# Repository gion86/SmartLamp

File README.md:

# SMART LAMP
### Smart lamp to wakeup with sunrise
##### SMD version

The project is a LED strip control board to generate a smart wakeup light, which 
simulates the sunrise light.
On board there is a real time clock, to  keep track of the actual date and time 
even on power loss, and some MOSFET to drive the LEDs with PWM.
On a separate breakout board I'm using a BLE chipset to connect with an Android 
application, to setup date, time, alarms and LED light.

Everything is soldered on the same PCB. The micro is an Atmel ATMega328P.

The project is compiled for Atmel AVR, with standard AVR GCC toolchain. 
Eclipse was used to create and compile the projects, with the AVR Eclipse Plugin.

This project consists of a main C++ file and some libraries:

* **DS3232RTC** : real time clock library, to read the actual date and time. The library 
  have been modified to work with the an external instance of the I2C bus control 
  class, and each functionality has been tested with the hardware (reference <https://github.com/gion86/DS3232RTC>);
* **TimeZone** : Arduino library to account for DST (summer time) with the RTC clock
  (reference <https://github.com/gion86/Timezone>, version with time.h from avr-libc);
* **Wire** : I2C library for Atmel micros. The library includes the correct source file for 
  the hardware used (reference <https://github.com/gion86/Wire>); 
  In the case of the Mega micro the I2C hardware module is used with the TwoWire 
  library (reference <https://github.com/esp8266/Arduino/tree/master/libraries/Wire>);
* **ATMega core**  (reference <https://github.com/gion86/ArduinoCore> and 
  <https://github.com/arduino/Arduino/tree/master/hardware/arduino/avr/cores/arduino>)

The project folder contains:

* Android application for Bluetooth Low Energy communication;
* the bill of material;
* datasheet of used components;
* electrical schematic and board (made with Eagle);

Some pictures can be found at https://photos.app.goo.gl/nYQq9dkLF3Ui9xUt2

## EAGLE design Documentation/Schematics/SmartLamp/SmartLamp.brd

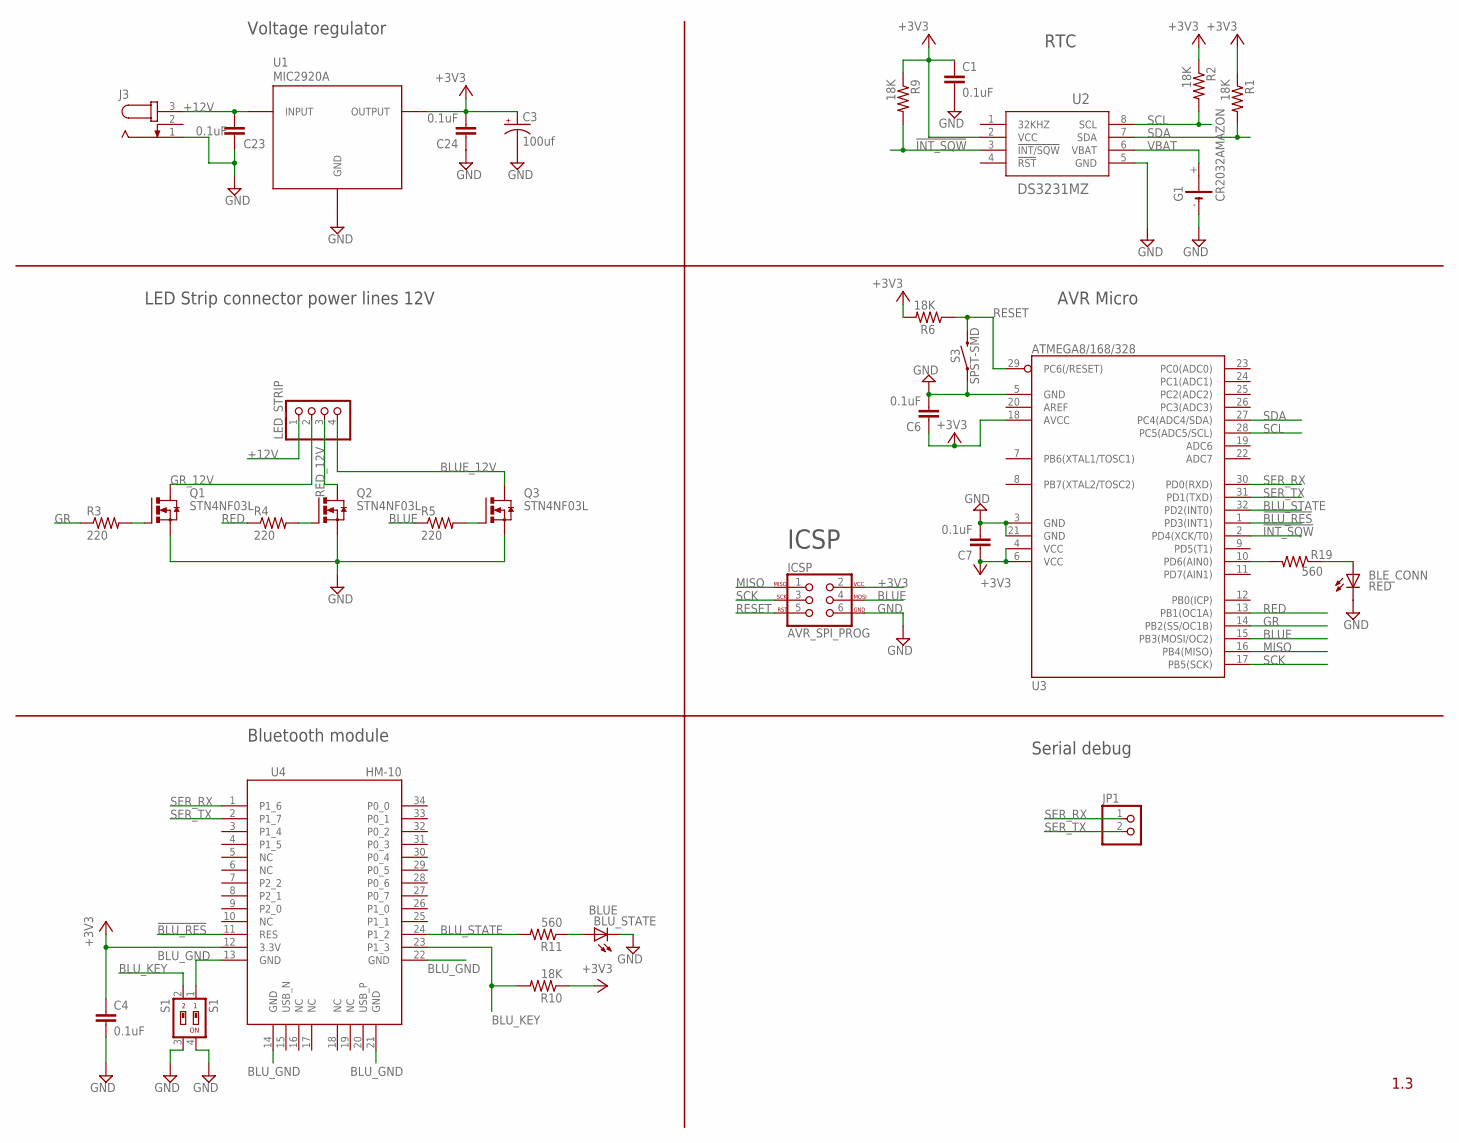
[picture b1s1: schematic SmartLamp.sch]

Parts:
BLE_CONN: RED; CHIPLED_1206
BLU_STATE: BLUE; CHIPLED_1206
C1, C4, C6, C7, C23, C24: 0.1uF; C1206
C3: 100uf; PANASONIC_C
G1: CR2032AMAZON; CR2032_AMAZON
ICSP: AVR_SPI_PROG; 2X3
J3: JACK-PLUG0; SPC4077
JP1: PINHD-1X2; 1X02
LED_STRIP: PINHD-1X4; 1X04
Q1, Q2, Q3: STN4NF03L; SOT223
R1, R2, R6, R9, R10: 18K; R1206
R3, R4, R5: 220; R1206
R11, R19: 560; R1206
S1: S1; SMS-002
S3: SPST-SMD; TACTILE_SWITCH_SMD_6.0X3.5MM
U1: MIC2920A; SOT-223
U2: DS3231MZ; 21-0041B_8
U3: ATMEGA8/168/328; TQFP32
U4: HM-10

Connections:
!BLU_RES: U3.1 (PD3(INT1)), U4.11 (RES)
!INT_SQW: R9.2, U2.3 (!INT/SQW), U3.2 (PD4(XCK/T0))
+3V3: C1.1, C3.+, C4.1, C6.1, C7.1, C24.2, ICSP.2, R1.1, R2.1, R6.2, R9.1, R10.1, U1.3 (OUTPUT), U2.2 (VCC), U3.4 (VCC), U3.6 (VCC), U3.18 (AVCC), U4.12 (3.3V)
+12V: C23.2, J3.3, LED_STRIP.1, U1.1 (INPUT)
BLUE: ICSP.4, R5.1, U3.15 (PB3(MOSI/OC2))
BLUE_12V: LED_STRIP.4, Q3.2 (D), Q3.4 (D)
BLU_GND: S1.1, U4.13 (GND), U4.14 (GND), U4.21 (GND), U4.22 (GND)
BLU_KEY: R10.2, S1.2, U4.23 (P1_3)
BLU_STATE: R11.2, U3.32 (PD2(INT0)), U4.24 (P1_2)
GND: BLE_CONN.C, BLU_STATE.C, C1.2, C3.-, C4.2, C6.2, C7.2, C23.1, C24.1, G1.-, ICSP.6, J3.1, Q1.3 (S), Q2.3 (S), Q3.3 (S), S1.3, S1.4, S3.1, U1.2 (GND), U1.TAB (GND), U2.5 (GND), U3.3 (GND), U3.5 (GND), U3.21 (GND)
GR: R3.1, U3.14 (PB2(SS/OC1B))
GR_12V: LED_STRIP.2, Q1.2 (D), Q1.4 (D)
MISO: ICSP.1, U3.16 (PB4(MISO))
unnamed: BLU_STATE.A, R11.1
unnamed: Q1.1 (G), R3.2
unnamed: Q2.1 (G), R4.2
unnamed: Q3.1 (G), R5.2
unnamed: R19.2, U3.10 (PD6(AIN0))
unnamed: BLE_CONN.A, R19.1
RED: R4.1, U3.13 (PB1(OC1A))
RED_12V: LED_STRIP.3, Q2.2 (D), Q2.4 (D)
RESET: ICSP.5, R6.1, S3.2, U3.29 (PC6(/RESET))
SCK: ICSP.3, U3.17 (PB5(SCK))
SCL: R2.2, U2.8 (SCL), U3.28 (PC5(ADC5/SCL))
SDA: R1.2, U2.7 (SDA), U3.27 (PC4(ADC4/SDA))
SER_RX: JP1.1, U3.30 (PD0(RXD)), U4.1 (P1_6)
SER_TX: JP1.2, U3.31 (PD1(TXD)), U4.2 (P1_7)
VBAT: G1.+, U2.6 (VBAT)

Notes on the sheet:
RTC
Voltage regulator
LED Strip connector power lines 12V
AVR Micro
ICSP
Bluetooth module
Serial debug

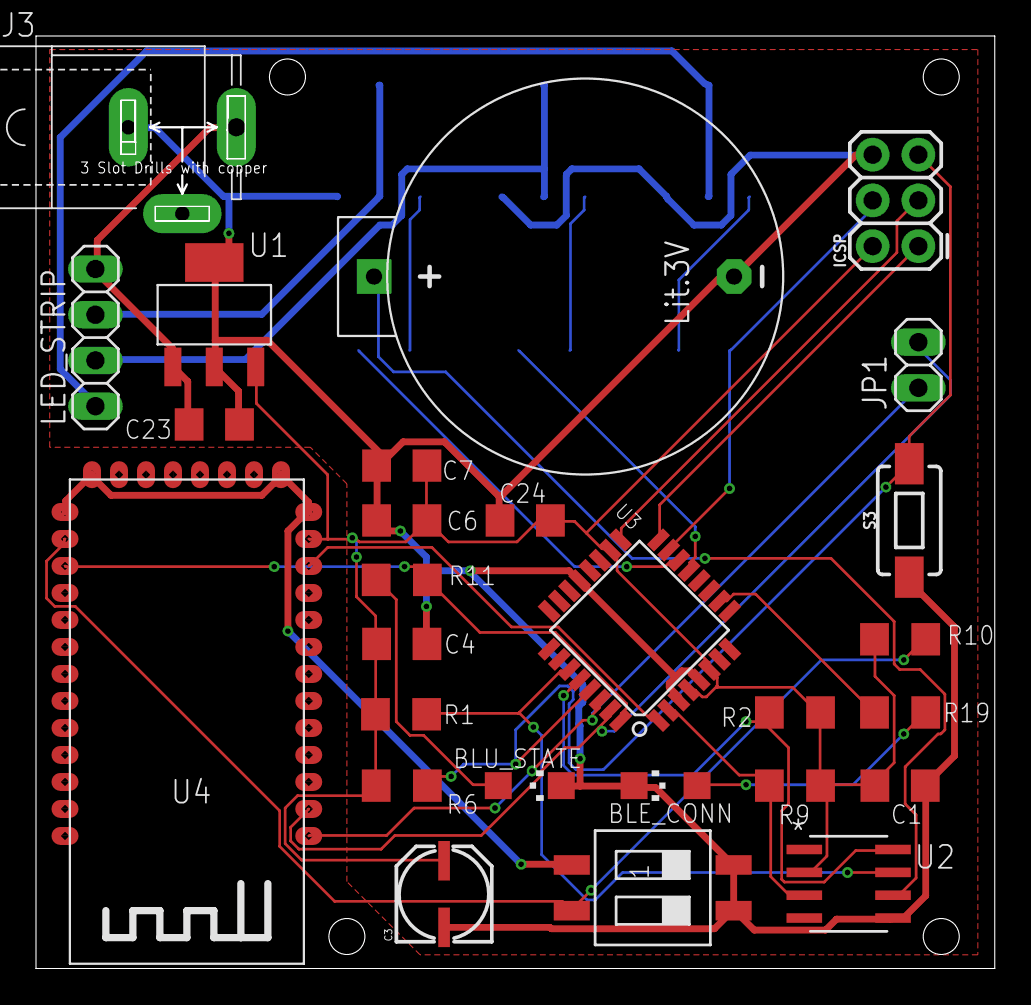
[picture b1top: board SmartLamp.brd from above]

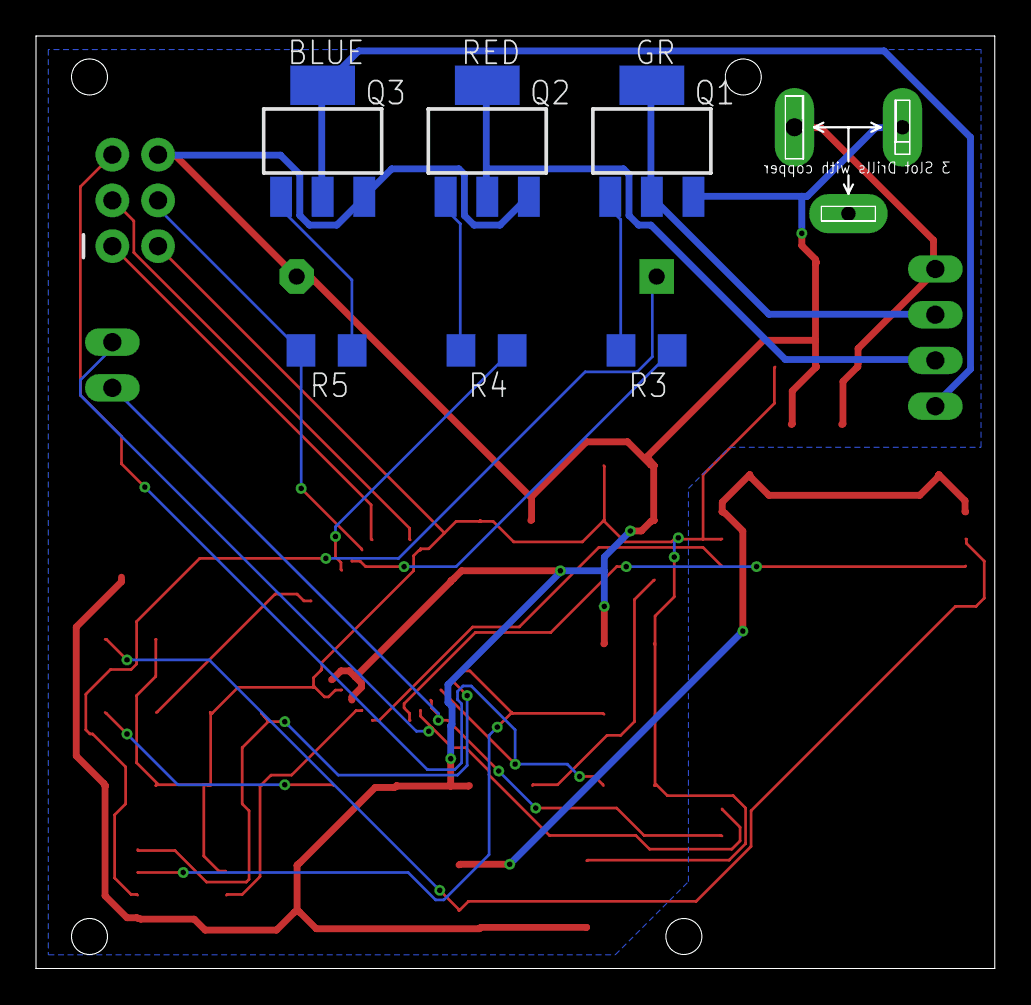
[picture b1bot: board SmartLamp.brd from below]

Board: 2 copper layers, 53.1 x 51.7 mm, 33 parts (6 on the bottom side), 28 nets.

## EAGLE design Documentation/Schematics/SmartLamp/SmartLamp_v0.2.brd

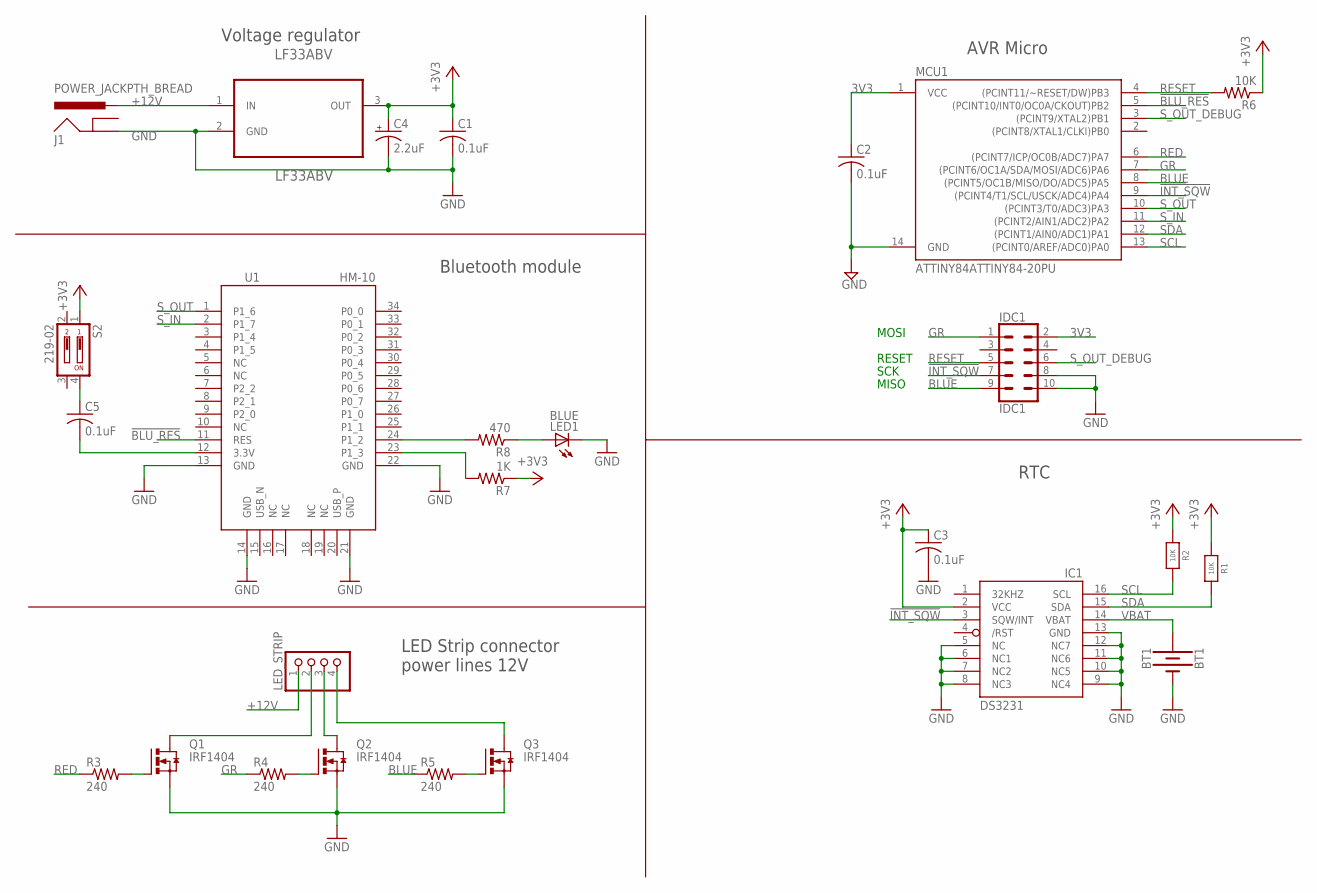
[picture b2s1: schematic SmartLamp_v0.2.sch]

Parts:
BT1: BT1; BATTCON_20MM_4LEGS
C1, C2, C3, C5: 0.1uF; C025-024X044
C4: 2.2uF; CPOL-RADIAL-10UF-25V
IC1: DS3231/SO; SO16W
IDC1: IDC1; 2X5-SHROUDED
J1: POWER_JACKPTH_BREAD; POWER_JACK_PTH_BREAD
LED1: BLUE; LED3MM
LED_STRIP: PINHD-1X4; 1X04
LF33ABV: LF33ABV; TO254P450X1020X1935-3P
MCU1: ATTINY84ATTINY84-20PU; DIL14
Q1, Q2, Q3: IRF1404; TO220BH
R1, R2: 10K; 0805-NO
R3, R4, R5: 240; 0207/10
R6: 10K; 0207/10
R7: 1K; 0207/10
R8: 470; 0207/10
S2: 219-02; CTS-219-02
U1: HM-10

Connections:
3V3: C2.1, IDC1.2, MCU1.1 (VCC)
!BLU_RES: MCU1.5 ((PCINT10/INT0/OC0A/CKOUT)PB2), U1.11 (RES)
!INT_SQW: IC1.3 (SQW/INT), IDC1.7, MCU1.9 ((PCINT4/T1/SCL/USCK/ADC4)PA4)
+3V3: C1.1, C3.1, C4.1 (+), IC1.2 (VCC), LF33ABV.3 (OUT), R1.1, R2.1, R6.1, R7.1, S2.1
+12V: J1.PWR, LED_STRIP.1, LF33ABV.1 (IN)
BLUE: IDC1.9, MCU1.8 ((PCINT5/OC1B/MISO/DO/ADC5)PA5), R5.1
GND: BT1.NEGATIVE (-), C1.2, C2.2, C3.2, C4.2 (-), IC1.5 (NC), IC1.6 (NC1), IC1.7 (NC2), IC1.8 (NC3), IC1.9 (NC4), IC1.10 (NC5), IC1.11 (NC6), IC1.12 (NC7), IC1.13 (GND), IDC1.8, IDC1.10, J1.GND, LED1.K (C), LF33ABV.2 (GND), MCU1.14 (GND), Q1.S, Q2.S, Q3.S, U1.13 (GND), U1.14 (GND), U1.21 (GND), U1.22 (GND)
GR: IDC1.1, MCU1.7 ((PCINT6/OC1A/SDA/MOSI/ADC6)PA6), R4.1
unnamed: C5.2, U1.12 (3.3V)
unnamed: C5.1, S2.4
unnamed: LED_STRIP.2, Q1.D
unnamed: LED_STRIP.3, Q2.D
unnamed: LED_STRIP.4, Q3.D
unnamed: Q1.G, R3.2
unnamed: Q2.G, R4.2
unnamed: R8.2, U1.24 (P1_2)
unnamed: LED1.A, R8.1
unnamed: Q3.G, R5.2
unnamed: R7.2, U1.23 (P1_3)
RED: MCU1.6 ((PCINT7/ICP/OC0B/ADC7)PA7), R3.1
RESET: IDC1.5, MCU1.4 ((PCINT11/~RESET/DW)PB3), R6.2
SCL: IC1.16 (SCL), MCU1.13 ((PCINT0/AREF/ADC0)PA0), R2.2
SDA: IC1.15 (SDA), MCU1.12 ((PCINT1/AIN0/ADC1)PA1), R1.2
S_IN: MCU1.11 ((PCINT2/AIN1/ADC2)PA2), U1.2 (P1_7)
S_OUT: MCU1.10 ((PCINT3/T0/ADC3)PA3), U1.1 (P1_6)
S_OUT_DEBUG: IDC1.6, MCU1.3 ((PCINT9/XTAL2)PB1)
VBAT: BT1.POSITIVE@1 (+), BT1.POSITIVE@2 (+), BT1.POSITIVE@3 (+), BT1.POSITIVE@4 (+), IC1.14 (VBAT)

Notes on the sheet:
MOSI
SCK
MISO
RESET
RTC
AVR Micro
Voltage regulator
Bluetooth module
LED Strip connector power lines 12V

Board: 2 copper layers, 26 parts (0 on the bottom side), 27 nets, no tracks yet.

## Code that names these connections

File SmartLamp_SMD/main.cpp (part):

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#define LED_GR             10   // RGB strip: green pin (PWM OCR1B)
#define LED_BLUE           11   // RGB strip: blue pin (PWM OCR2A)

#define BLU_STATE           2   // BLE module state pin
#define BLU_RESET           3   // BLE module reset pin

#define RTC_INT_SQW         4   // INT/SQW pin from RTC
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static void setupPWM() {
  // Fast PWM
  
  // PB1, PB2, PB3 output mode done in setup()

  // Setup Fast PWM mode using MAX as TOP (8bit) 
  TCCR1A &= ~(1 << WGM11);
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  pinMode(LED_BLUE, OUTPUT);
  pinMode(LED_GR, OUTPUT);
  pinMode(LED_RED, OUTPUT);
  pinMode(BLU_STATE, INPUT);
  pinMode(BLU_RESET, OUTPUT);
  pinMode(RTC_INT_SQW, INPUT);
  pinMode(BLU_LED, OUTPUT);
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      Serial.println(led_value);
#endif

      // PWM duty cycle on pins PB1, PB2, PB3: the value is scaled by the current
      // alarm color.
      OCR1A = led_value * alarms[systemTime.tm_wday].ledColor[0] / 255;
      OCR1B = led_value * alarms[systemTime.tm_wday].ledColor[1] / 255;
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
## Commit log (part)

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2017-09-13 Added first version of Eagle schematics
2017-09-13 Added regulator and bluetooth module to schematic
2017-09-14 Small changes to schematic
2017-09-16 Complete first version of schematic and board. Added first partlist and BOM
2017-09-17 Modified switch and RGB connection
2017-09-18 Fixed IDC connector and replaced switch
2017-09-18 Revisited board, ERC on schematic
2017-09-24 Added datasheet, replaced 2.2uf cap on schematic with 100uf, to program the Tiny at 3.3v. Added Arduino communication test with HM-10 module.
2017-09-24 Updated partlist
2017-09-26 Replaced SMD resistors with TH, for this version of the board.
2017-09-29 Updated datasheets.
2017-10-01 Added datasheet for new mosfet IRLZ44n, small changes to HM-10 test program.
2017-10-05 Changed dip switch to cut GND instead of VCC to bluetooth module.
2017-10-07 Added reference to RTC library, to be tested on hardware.
2017-10-08 Fixed IO connections to micro, in schematic and main.cpp
2017-10-08 Fixed IO connections to micro, in schematic.
2017-10-08 Fixed cap on HM-10 module...
2017-10-08 Fixed project reference, added calibrated OSSCAL value in main.
2017-10-11 Fixed 3.3V path in schematic
2017-10-13 Revisited sleep cycle, added Link-time optimization options.
2017-10-14 Added USIWire include and link.
2017-10-14 Fixed project references. Changed reference to include NeoSWSerial library instead of SoftwareSerial. Changed serial parsing code: it seems more reliable now...
2017-10-14 Removed Release cfg for now..
2017-10-16 Fixed input/output pins and synch with schematic. Added PCINT interrupt on INT_SQW line from RTC
2017-10-16 Removed SoftwareSerial library! Used CORE Serial instead. Fixed ISR(PCINT0_vect) call, enable PCINT0 and PCINT2 interrupt. Reviewed input/output pins.
2017-10-17 Fixed output pins to use PWM... ops. Added PWM test cycle.
2017-10-18 First tests with RTC and DS3232RTC and TinyWireM libraries. Added set times, added Alarms, tested wakeup from INT pin (RTC).
2017-10-18 Added license and version
2017-10-20 Converted RTc lib to use time.h from avr-libc.
2017-10-20 Year..
2017-10-20 Comments.
2017-10-21 Completed porting to time.h avr-libc library, and added reference do TimeZone library (also ported ti time.h avr-libc library)
2017-10-21 Fixed IDC connection (ISP programmer). Completed routing, added ground and signal plane.
2017-10-21 Added text in silk, added gerber files.
2017-10-21 Updated Eagle project.
2017-10-22 Changed position of dec capacitor on brd
2017-10-22 New device for CC2514, first routed version of the board. Still clearence problem on the device!
2017-10-22 Changed GND traces width, modified ground and power planes.
2017-10-23 First version of fade algorithm with cos() function. Added state machine to loop.
2017-10-25 Routing of the board in progress.. new version with ATMega168/328P
2017-10-26 Eagle main file...
2017-10-29 Changed micro package, added IDC connector, replace regulatot. Some component to be checked
2017-10-30 Renamed project and project folder
2017-10-30 Changed pinout for atmega.
2017-11-01 Added function documentation and power reduction options
2017-11-01 Fixed sleep timeout.
2017-11-02 New BOM, with updated format. Fixed schematich and re-routed board
2017-11-06 Added command parsing from BLE serial (untested)
2017-11-06 Added datasheets
2017-11-09 Updated schetaic, board and partlit with AVR ISP connector and MOSFET on the bottom layer
2017-11-11 Arranged label with smashed part on schematic and board
2017-11-13 Updated partlis, addde communication protocol specification, added alarm structure, filling code, eeprom save, loop code cleaned.
2017-11-16 Updated partlist from Ebay
2017-11-22 Schematic anb board v1.0: gerber file and png generated.
2017-11-22 Fixed bottom silkscreen, updated partlist with pcb board.
2017-11-29 Added data checks in parseCommand(). Removed EEPROM time rules load.
2017-11-29 Fixed array copy with memcpy()
2017-12-09 First commit of BLE application: code and settings imported from BLE example on Google Developers
2017-12-10 Added UART service, revisited DeviceControlActivity code, first attempt to write a GATT characteristic. Removed old service class and GATT attributes class.
2017-12-17 Reorganized service code, cleaned up a bit.
2017-12-17 Changed end of line for bat files
2017-12-24 Added buttons on view to test serial connectivity, added UTC date and time set, added 20 byte parsing on receive.
2017-12-24 Updated communication protocol with year, month, day, added "OK" ack, TEST WITH ATMEGA328 (not P).
2017-12-26 First working version of setNextAlarm, based on the actual system time and the next alarm in chronological order. Removed seconds from alarm structure.
2017-12-26 Added printAlarm for debug, fixed void * in memset calls, modified protocol for fadeTime value. Added option to set EESAVE bit in fuse to preserve EEPROM content.
2017-12-26 Removed "send" call on test button pressed.
2017-12-30 LED fade test start... added debug and "prevMillis".
2017-12-31 Added activity for day alarm, navigation drawer, settings. First step for app navigation..
2017-12-31 Moved classe in packages, implemented first version of ArrayListAdapter, with custom views. Tested with some data. Added model class DayAlarm.java.
2018-01-01 Adeded DB schema (JSON), first version of DB Junit test, created DB in AlarmActivity.java, to test.
2018-01-02 Started port to Room APIs, model MVVM, renamed packages and created model, viewmodel, adapter and recycleview..
2018-01-03 Fixed bug in RecycleView layout, completed first version of Room components as per Android dev recommendations. Added test cases and data.
2018-01-14 Added actionbar (support) in activity and preferences. Implemented callback interface in adapter, to be finished.
2018-01-14 Implemented callback interface from adapter to activity for all the layout fields.
2018-01-14 Added weekdays in the database and modified layout to fit everything on the screen.
2018-01-19 Added Pololu programmer config, added check for EEPROM default value at startup.
2018-01-20 Implemented callback interface from adapter to activity for RecycleView items clicks. Added custom AlertDialog for fade time user input.
2018-01-20 Added command "AL_WD_hhmm_fd" to specify fade time. To be tested
2018-01-27 Added AsynckTask on service to send data, added ack check on receive, fixed service leak on AlarmActivity, still problem on the service "auto close"...
2018-01-27 Activity set to singleTop for now, to keep it alive for the service bind. Fixed line separator and added no connection error in service
2018-01-27 Removed some debug prints, test for wakeup in progress
2018-01-28 Added menu and code in AlarmActivity.java to manage service connection and lifecycle. Added automatic messagge on first connection, to be tested.
2018-01-28 Fixed DC jack and battery holder footprint.. milling level needed for slot holes.
2018-01-29 Fixed GND - switch connection for HM-10
2018-01-29 Added Release configuration for real PCB hardware
2018-02-04 Added PWM configuration and code in FADE step, tested on breadboard, Added BLU_RESET startup bit value. Fixed red led flash in case of error in setup()
2018-02-05 Changed timer 1 cfg to 8bit and added timer 2 at 8bit PWM, to use PB1,PB2, PB3 output. Testing with log() function and LLED strip.
2018-02-06 Updated Eclipse project references
2018-02-10 Added max brightness define and used x³ as function for LEDs. Hardware complete, working OK with BLE!!
2018-02-10 Added command output from parseCommand, added TEST command, fixed fadeTime read from BLE.
2018-02-10 Added micro reset button.
2018-02-18 Added color picker in new activity, tested with PCB.
2018-02-19 Added led color in alarm structure: one different color for each alarm. Removed useless data checks in parseCommand(), added RGB component to alarm full command.
2018-02-19 Added parse code to parse the end of line char from Serial. Removed some debug output.
2018-02-20 Replaced color picker with jaredrummler color picker, revisited RGBActivity.java code, updated model and adapter to have color update in DB. Added circle shape to day_item.xml,
2018-02-20 Renamed member variables.
2018-02-20 Added test eand exit buttons to serial_read_write.xml
2018-02-24 Implemented action "no UART support in service", removed first write, it seems not needed, removed menu from DeviceControlActivity.java
2018-02-24 Addded connected state to NavigationDrawerFragment, adn implemented a custom ArrayAdapter to disable muen items. Fixed titles on the activities.
2018-02-24 Added runtime check on DayAlarm.java constructors, and refactored.
2018-02-24 Started to refactor preference code: removed unsed section, still en exception on the "general" section..
2018-02-25 Completed preference read and save from AlarmActivity!
2018-02-25 Fixed laytou scroll in serial_read_write.xml and layout width in day_item.xml. Version code starting v0.5: first test on P10 device.
2018-02-25 Added toast on all command sent, cleaned strings.xml, added timeout on connect dialog, fixed set hour and minute clear color.
2018-02-25 Replaced deprecated API in DeviceScanActivity.java (BlueToothLeScanner), added ACTIOn in BLESerialPortService.java to broadcast info on cmd send and ack. Added ProgressDialog in AlarmActivity.java to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
2018-02-25 Completely replaced ASyncTask with Handler in its onw thread in BLESerialPortService.java. Fixed some Lint warnings.
2018-02-25 Fixed nonnull and final warning from Lint, and others. Fixed layout weight, fixed test alignment in textview.
2018-02-27 Added permission and location service request code to enable "BLE scan" on Android 7+ (http://developer.radiusnetworks.com/2015/09/29/is-your-beacon-app-ready-for-android-6.html). Fixed activity_alar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
2018-03-03 Added CC2541 breakout board PCB for reference, cleaned up gitignore in root
2018-03-04 Added release data to populate DB on first install in DBData.java, and static method with DEBUG check. Fixed behaviour when BL controller not enabled, changed application name
2018-03-04 Added release folder to gitignore
2018-03-05 Replaced some deprecated method in NavigationDrawerFragment.java, fixed NULL pointer in AlarmActivity.java on device scan menu item selected.
2018-03-10 Added BroadcastReceiver for ACK timeout in activities, removed BLE.connect in service callbacks (useless), fixed wrong timeout message on empty queue (BLE service). Fixed different Lint warning in co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
2018-03-11 Added print command, cleaned debug output, changed EEPROM write to save only the modified alarm struct (main.cpp).
2018-03-11 Revisited layout for DeviceDebugActivity.java activity: log with date, autoscroll, menu to clean. Added "PRINT" command to display current alarm data from MCU.
2018-03-11 Fixed buttons layout with "weight", fixed empty command sent.
2018-03-18 Added options support: time on and led brightness on the micro code, to be tested.
2018-03-18 Added NumberPickerPreference.java for number preferences in new section pref_led.xml. Added ProtocolUtil method and settings in AlarmActivity.java, to be tested on hardware.
2018-03-19 Added printOptions() and debug print. Fixed default value for options.
2018-04-26 Updated gradle plugin and app build configuration (as per https://developer.android.com/studio/build/gradle-plugin-3-0-0-migration?utm_source=android-studio#new_configurations).
2018-04-30 Moved some components datasheet into new repo
2018-04-30 Added cache folder to gitignore
2018-05-17 Replaced ICSP connector with 3x2, added a separete serial RT TX connector
2018-06-02 First sketch for the 3D box!!!!!!!!!1
2018-06-02 Added screw hole in the box
2018-06-05 Modified slot in milling level for DC connector. Made gerber for board file v1.3
2018-06-08 Added text message for slot drills on board file
2018-06-10 Added screw holes for PCB in box
2018-11-18 Renamed some function to be uniform with other projects.
2020-03-22 Updated gradle plugin and app build configuration. Added debug activity DebugActivityUnitTest.java.
2020-03-22 Updated gradle plugin and app build configuration.

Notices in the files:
SmartLamp_SMD/main.cpp:
Licensed under the Apache License, Version 2.0 (the "License");
parts and their libraries:
SparkFun-Connectors: Licensing: Creative Commons ShareAlike 4.0 International - https://creativecommons.org/licenses/by-sa/4.0
microbuilder: This work is placed in the public domain, and may be freely used for commercial and non-commercial work with the following conditions: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
